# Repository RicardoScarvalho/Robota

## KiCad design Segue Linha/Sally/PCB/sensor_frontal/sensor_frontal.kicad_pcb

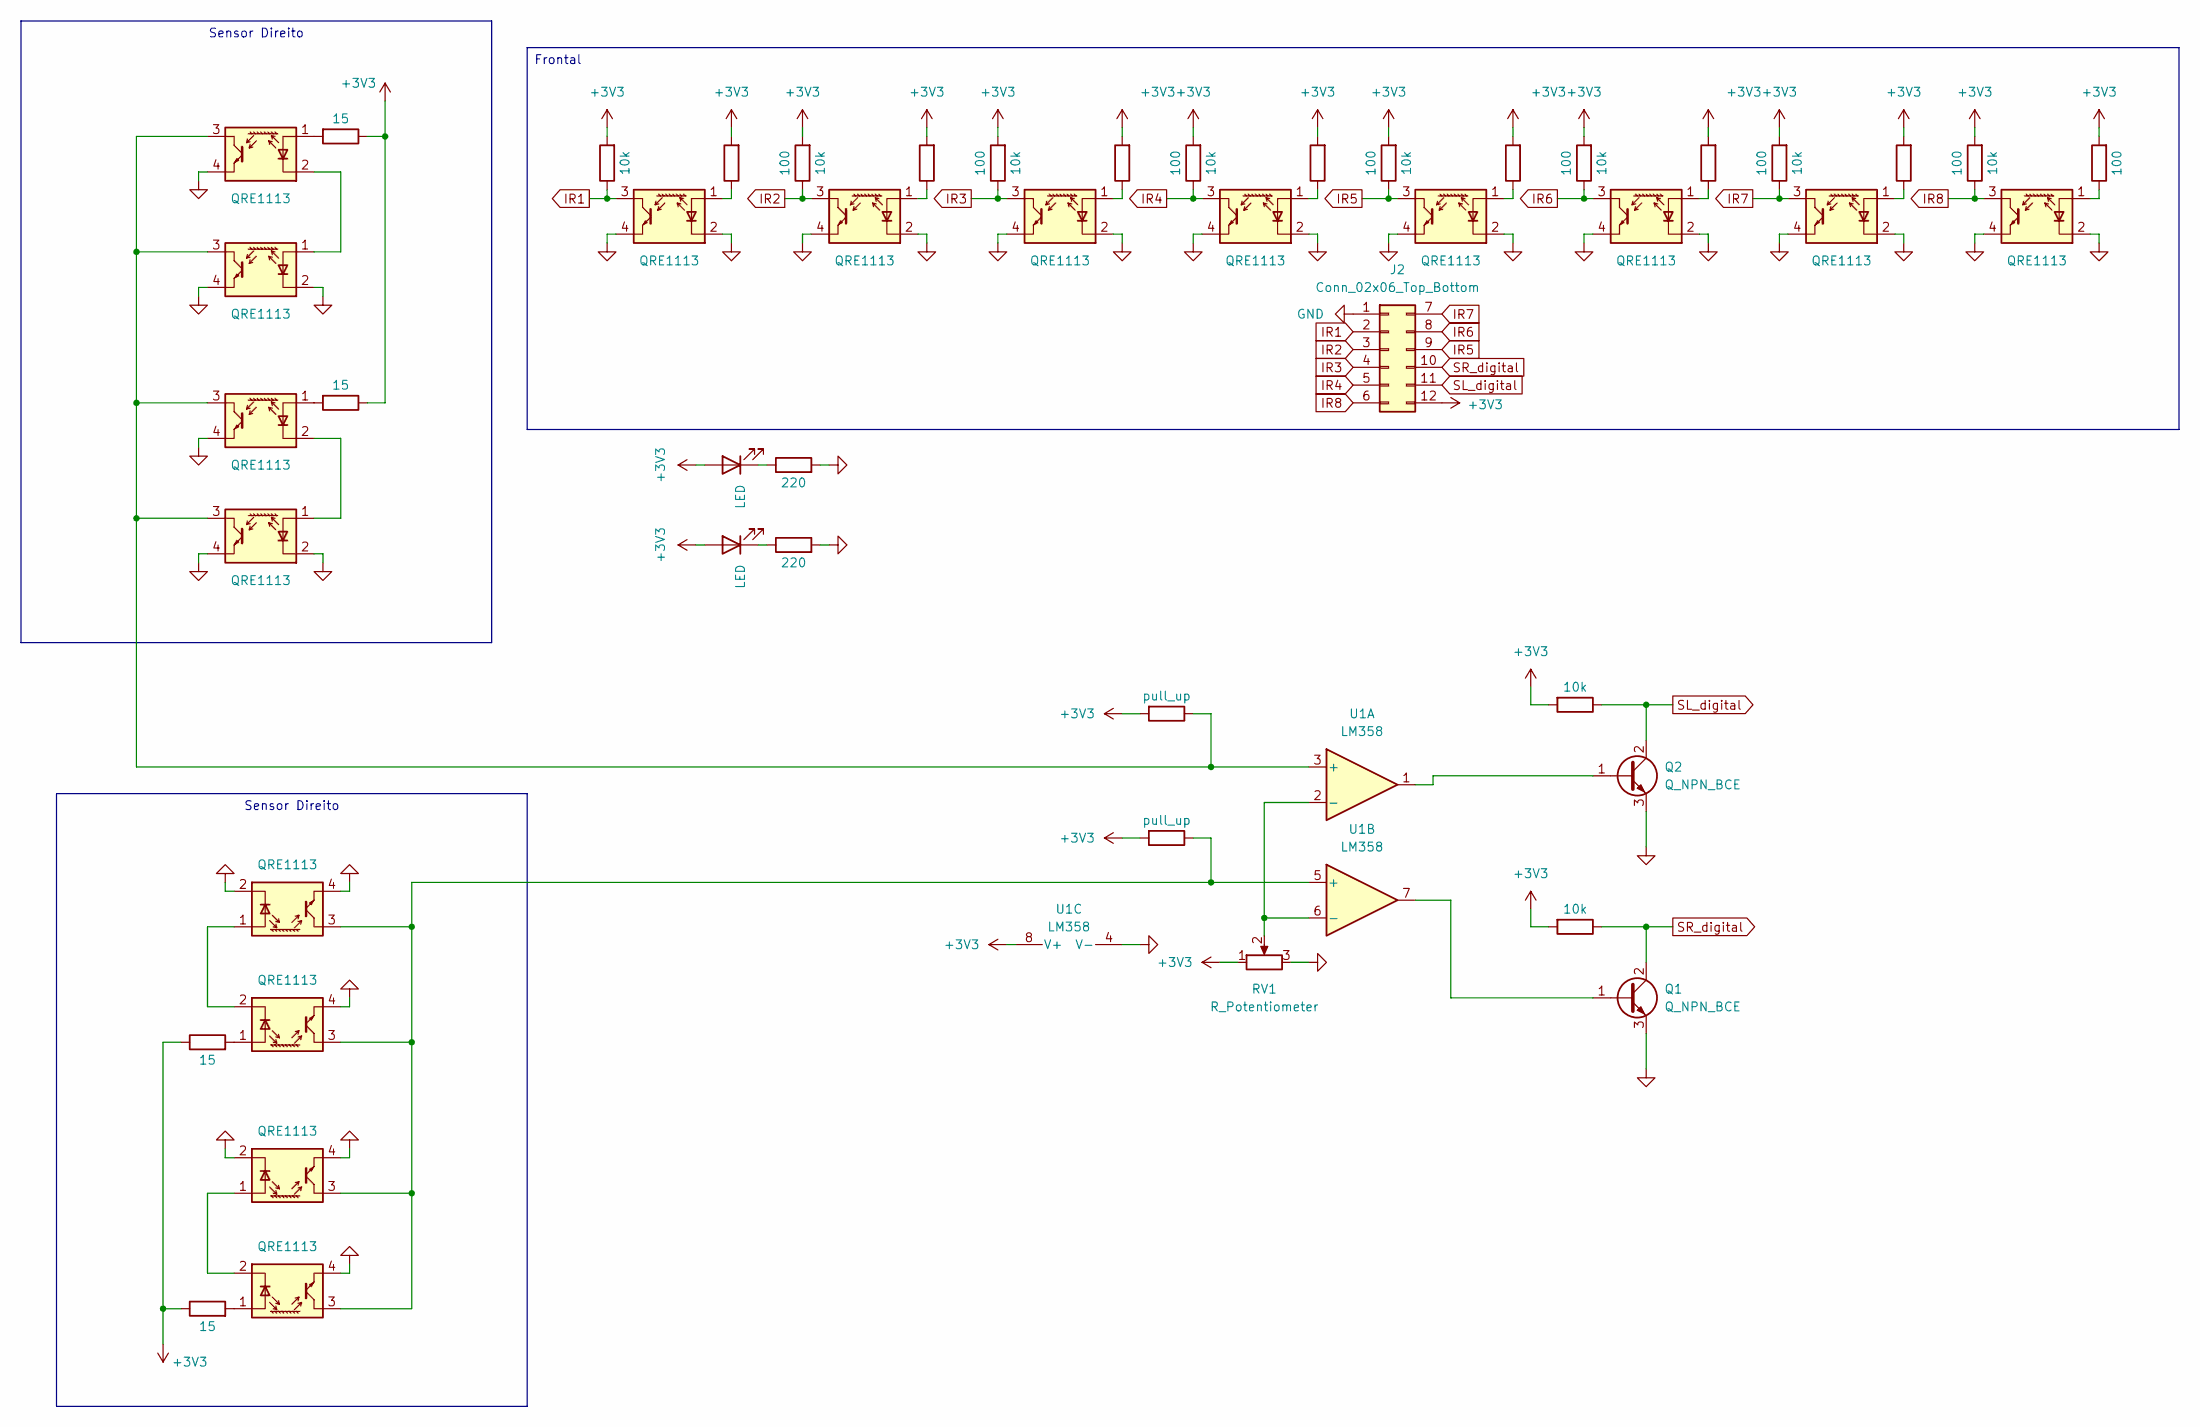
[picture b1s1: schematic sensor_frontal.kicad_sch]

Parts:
D4, D5: LED; LED_1206_3216Metric
J2: Conn_02x06_Top_Bottom; Hirose_FH12-12S-0.5SH_1x12-1MP_P0.50mm_Horizontal
Q1, Q2: Q_NPN_BCE; SOT-23
R11, R12, R29, R31, R32, R33, R34, R35, R44, R47: 10k; R_1206_3216Metric
R16, R18, R20, R21: 15; R_1206_3216Metric
R25, R26: 220; R_1206_3216Metric
R36, R37, R38, R39, R40, R41, R42, R43: 100; R_1206_3216Metric
R45, R46: pull_up; R_1206_3216Metric
RV1: R_Potentiometer; Potentiometer_Bourns_3314G_Vertical
U1: LM358; SOIC-8_3.9x4.9mm_P1.27mm
U5, U6, U7, U8, U11, U12, U13, U14, U15, U16, U17, U18, U19, U20, U21, U22: QRE1113; OnSemi_CASE100CY

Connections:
+3V3: D4.2 (A), D5.2 (A), J2.12, R11.2, R12.2, R16.1, R18.1, R20.1, R21.1, R29.2, R31.2, R32.2, R33.2, R34.2, R35.2, R36.2, R37.2, R38.2, R39.2, R40.2, R41.2, R42.2, R43.2, R44.2, R45.2, R46.2, R47.2, RV1.1, U1.8 (V+)
GND: J2.1, Q1.3 (E), Q2.3 (E), R25.2, R26.2, RV1.3, U1.4 (V-), U5.4, U6.2 (K), U6.4, U7.4, U8.2 (K), U8.4, U11.2 (K), U11.4, U12.4, U13.2 (K), U13.4, U14.4, U15.2 (K), U15.4, U16.2 (K), U16.4, U17.2 (K), U17.4, U18.2 (K), U18.4, U19.2 (K), U19.4, U20.2 (K), U20.4, U21.2 (K), U21.4, U22.2 (K), U22.4
IR1: J2.2, R11.1, U11.3
IR2: J2.3, R12.1, U16.3
IR3: J2.4, R29.1, U17.3
IR4: J2.5, R31.1, U18.3
IR5: J2.9, R32.1, U19.3
IR6: J2.8, R33.1, U20.3
IR7: J2.7, R34.1, U21.3
IR8: J2.6, R35.1, U22.3
unnamed: D4.1 (K), R25.1
unnamed: D5.1 (K), R26.1
unnamed: Q1.1 (B), U1.7
unnamed: Q2.1 (B), U1.1
unnamed: R45.1, U1.3 (+), U5.3, U6.3, U7.3, U8.3
unnamed: RV1.2, U1.2 (-), U1.6 (-)
unnamed: R46.1, U1.5 (+), U12.3, U13.3, U14.3, U15.3
unnamed: R18.2, U5.1 (A)
unnamed: U5.2 (K), U6.1 (A)
unnamed: R16.2, U7.1 (A)
unnamed: U7.2 (K), U8.1 (A)
unnamed: R36.1, U11.1 (A)
unnamed: R21.2, U12.1 (A)
unnamed: U12.2 (K), U13.1 (A)
unnamed: R20.2, U14.1 (A)
unnamed: U14.2 (K), U15.1 (A)
unnamed: R37.1, U16.1 (A)
unnamed: R38.1, U17.1 (A)
unnamed: R39.1, U18.1 (A)
unnamed: R40.1, U19.1 (A)
unnamed: R41.1, U20.1 (A)
unnamed: R42.1, U21.1 (A)
unnamed: R43.1, U22.1 (A)
SL_digital: J2.11, Q2.2 (C), R47.1
SR_digital: J2.10, Q1.2 (C), R44.1

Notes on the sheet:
Sensor Direito
Frontal

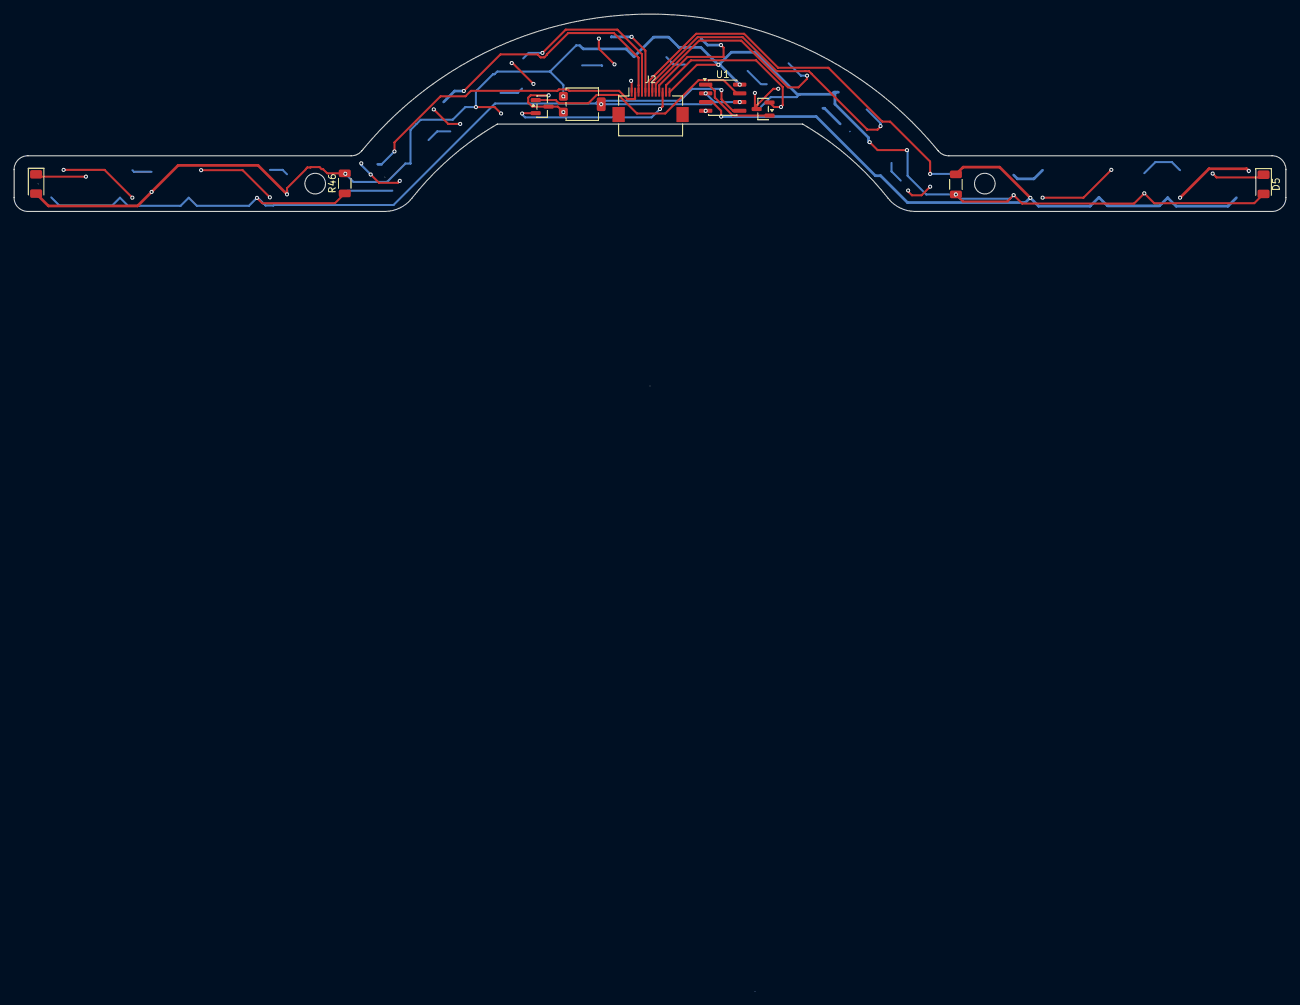
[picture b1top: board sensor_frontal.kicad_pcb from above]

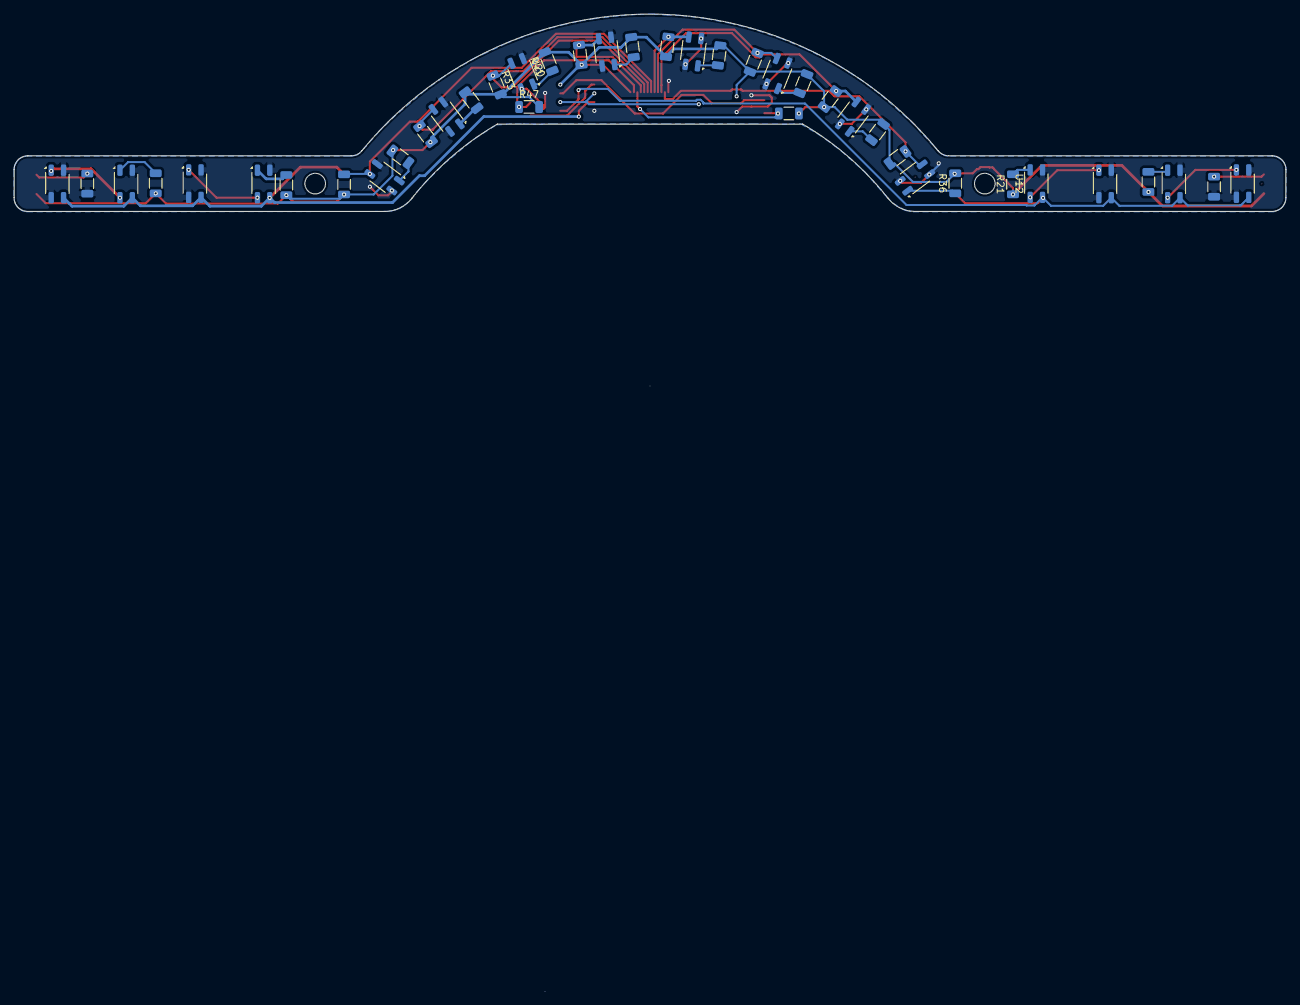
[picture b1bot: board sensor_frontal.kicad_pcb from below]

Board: 2 copper layers, 185.0 x 142.1 mm, 49 parts (40 on the bottom side), 35 nets.

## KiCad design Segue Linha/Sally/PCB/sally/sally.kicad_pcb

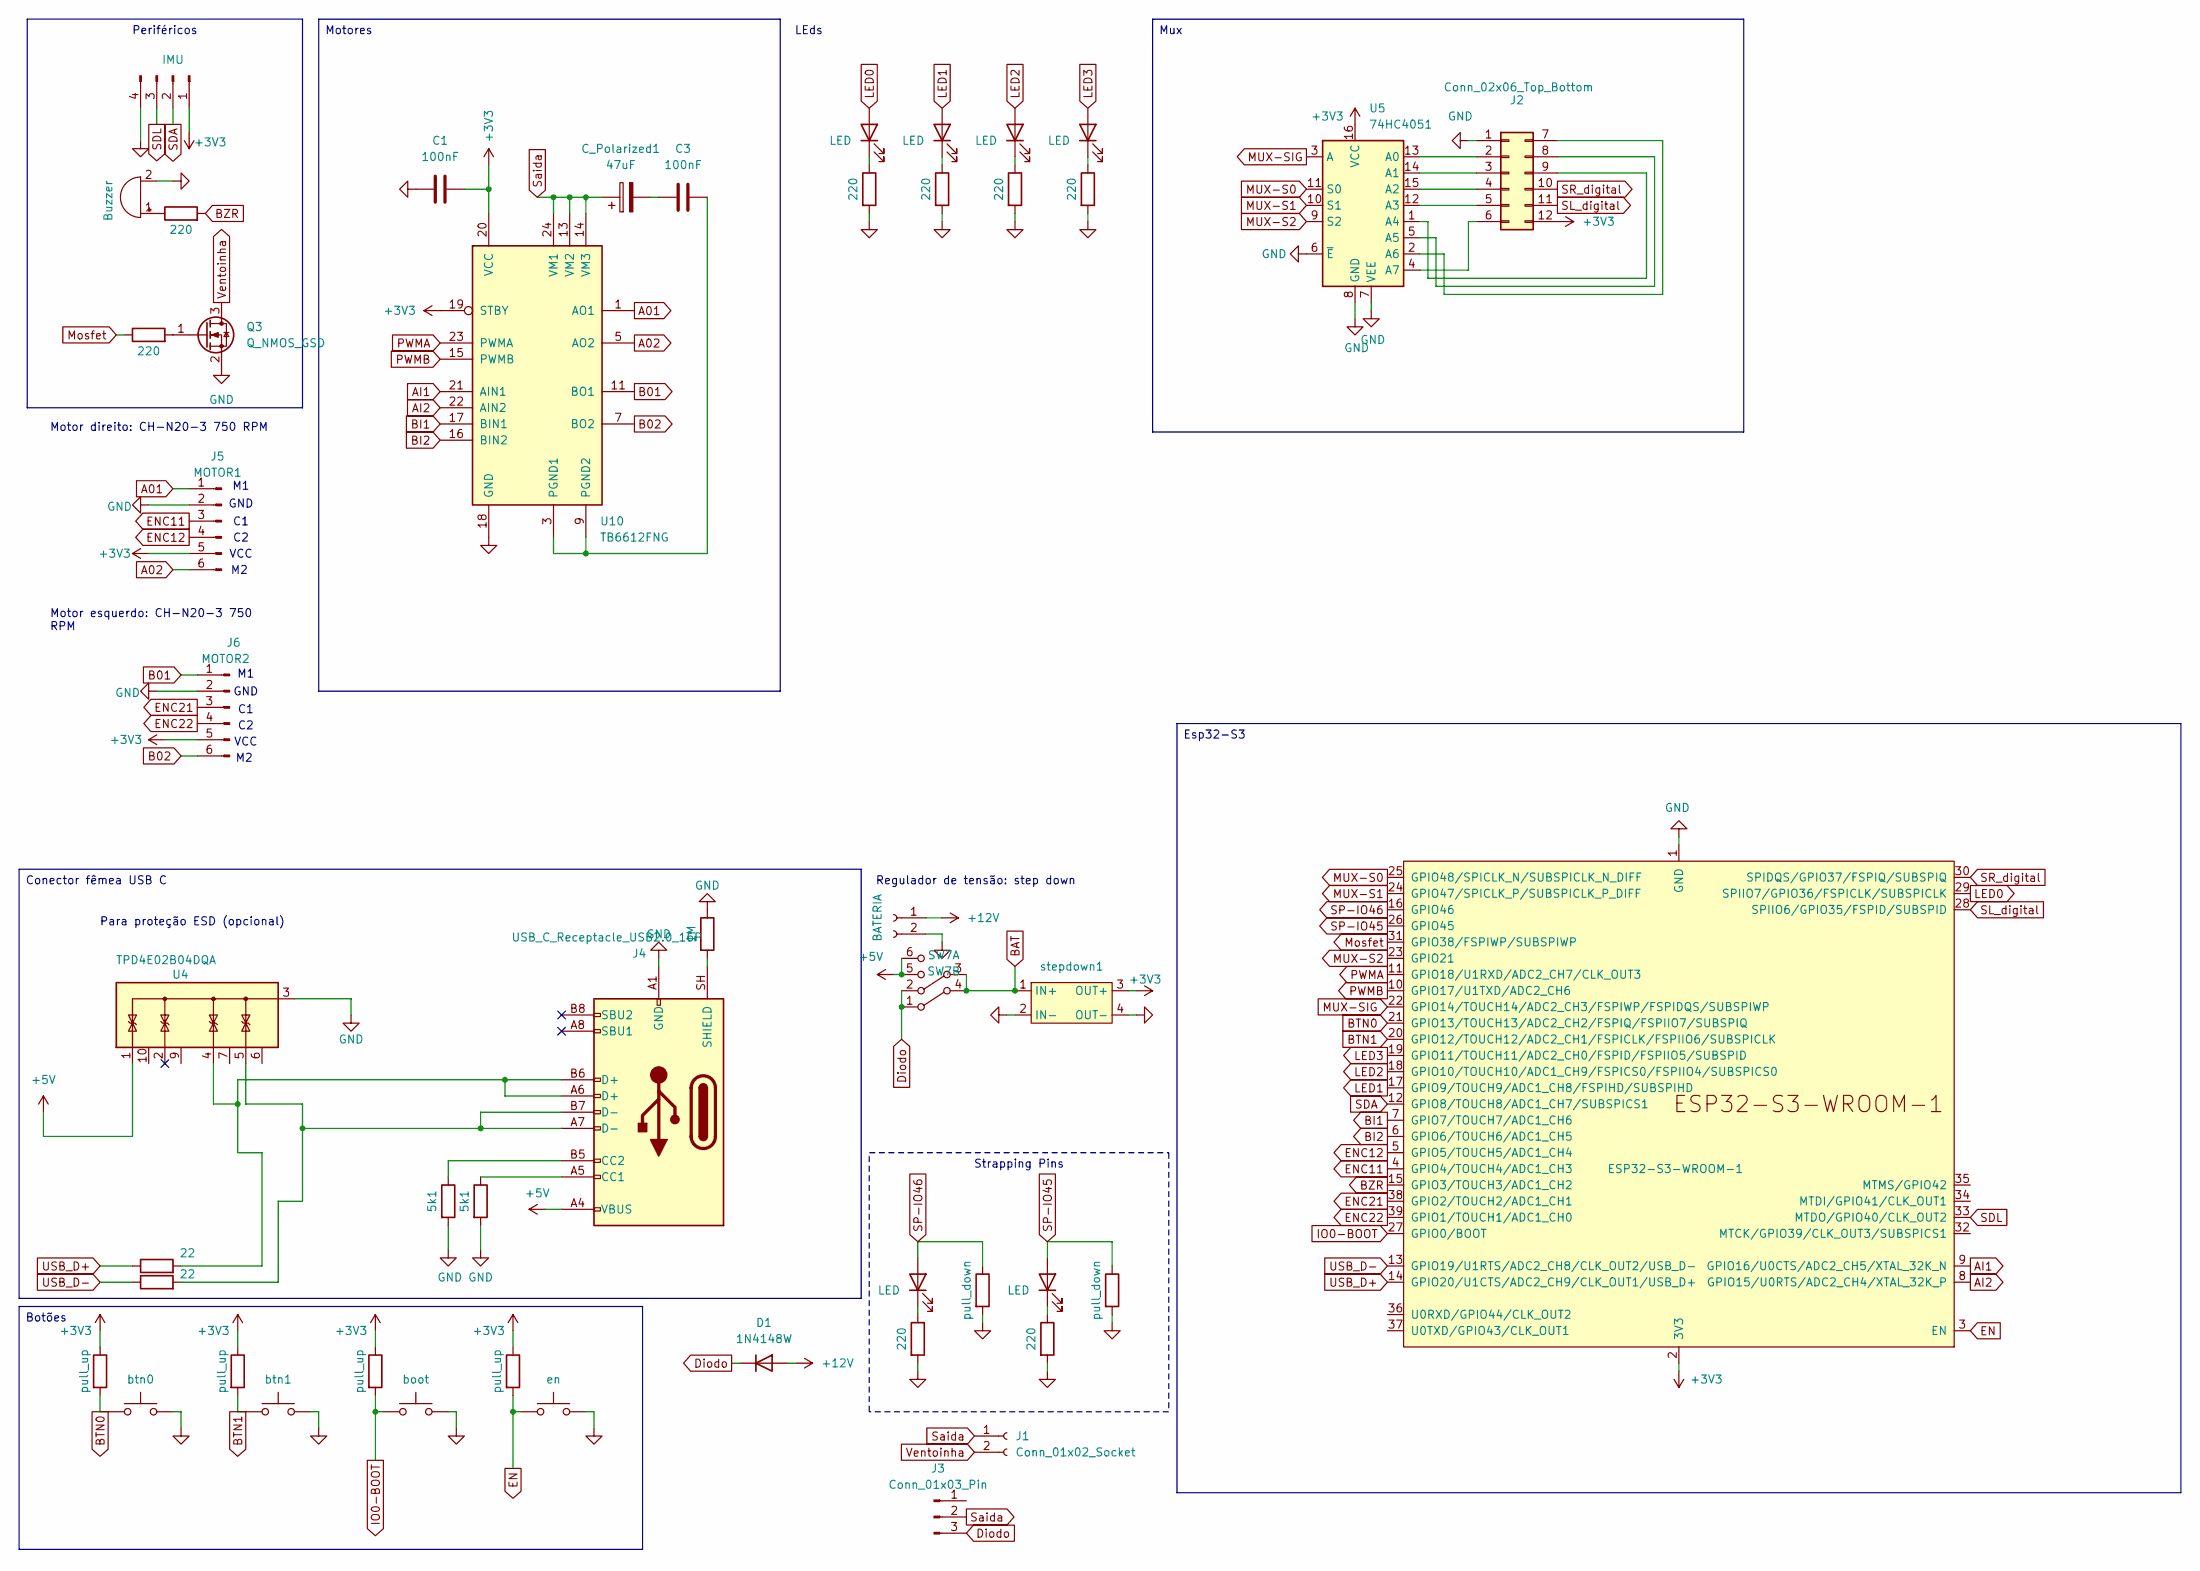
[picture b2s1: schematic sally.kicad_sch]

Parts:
BZ1: Buzzer; Buzzer_12x9.5RM7.6
C1, C3: 100nF; C_0805_2012Metric
C_Polarized1: 47uF; CP_Radial_D6.3mm_P2.50mm
D1: 1N4148W; D_SOD-123
D2, D3, D4, D5, D6, D7: LED; LED_1206_3216Metric
J1: Conn_01x02_Socket; PinHeader_1x02_P2.54mm_Vertical
J2: Conn_02x06_Top_Bottom; Hirose_FH12-12S-0.5SH_1x12-1MP_P0.50mm_Horizontal
J3: Conn_01x03_Pin; PinHeader_1x03_P2.54mm_Vertical
J4: USB_C_Receptacle_USB2.0_16P; USB_C_Receptacle_GCT_USB4085
J5: MOTOR1; PinHeader_1x06_P2.54mm_Vertical
J6: MOTOR2; PinHeader_1x06_P2.54mm_Vertical
Q3: Q_NMOS_GSD; SOT-23
R1, R3: 22; R_1206_3216Metric
R2, R24: 5k1; R_1206_3216Metric
R4, R6, R10, R25, R26, R27, R28, R30: 220; R_1206_3216Metric
R5, R7: pull_down; R_1206_3216Metric
R8, R9, R19, R22: pull_up; R_1206_3216Metric
R23: 1M; R_1206_3216Metric
SW1: btn0; SW_PUSH_6mm
SW2: btn1; SW_PUSH_6mm
SW3: boot; SW_PUSH_6mm
SW4: en; SW_PUSH_6mm
SW7: SW_DPDT_x2; PinHeader_2x03_P2.54mm_Vertical
U1: ESP32-S3-WROOM-1
U4: TPD4E02B04DQA; USON-10_2.5x1.0mm_P0.5mm
U5: 74HC4051; SOIC-16_3.9x9.9mm_P1.27mm
U10: TB6612FNG; SSOP-24_5.3x8.2mm_P0.65mm
con1: BATERIA; Molex_KK-254_AE-6410-02A_1x02_P2.54mm_Vertical
con6: IMU; PinHeader_1x04_P2.54mm_Vertical
stepdown1: stepdown

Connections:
+3V3: C1.2, J2.12, J5.5, J6.5, R8.1, R9.1, R19.1, R22.1, U1.2 (3V3), U5.16 (VCC), U10.19 (STBY), U10.20 (VCC), con6.1, stepdown1.3 (OUT+)
+5V: J4.A4 (VBUS), J4.A9 (VBUS), J4.B4 (VBUS), J4.B9 (VBUS), SW7.5 (C), SW7.6 (C), U4.1 (IO1)
+12V: D1.2 (A), con1.1
A01: J5.1, U10.1 (AO1), U10.2 (AO1)
A02: J5.6, U10.5 (AO2), U10.6 (AO2)
AI1: U1.9 (GPIO16/U0CTS/ADC2_CH5/XTAL_32K_N), U10.21 (AIN1)
AI2: U1.8 (GPIO15/U0RTS/ADC2_CH4/XTAL_32K_P), U10.22 (AIN2)
B01: J6.1, U10.11 (BO1), U10.12 (BO1)
B02: J6.6, U10.7 (BO2), U10.8 (BO2)
BAT: SW7.3 (B), SW7.4 (B), stepdown1.1 (IN+)
BI1: U1.7 (GPIO7/TOUCH7/ADC1_CH6), U10.17 (BIN1)
BI2: U1.6 (GPIO6/TOUCH6/ADC1_CH5), U10.16 (BIN2)
BTN0: R8.2, SW1.1, U1.21 (GPIO13/TOUCH13/ADC2_CH2/FSPIQ/FSPIIO7/S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)
BTN1: R9.2, SW2.1, U1.20 (GPIO12/TOUCH12/ADC2_CH1/FSPICLK/FSPIIO6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)
BZR: R10.2, U1.15 (GPIO3/TOUCH3/ADC1_CH2)
Diodo: D1.1 (K), J3.3, SW7.1 (A), SW7.2 (A)
EN: R22.2, SW4.1, U1.3 (EN)
ENC11: J5.3, U1.4 (GPIO4/TOUCH4/ADC1_CH3)
ENC12: J5.4, U1.5 (GPIO5/TOUCH5/ADC1_CH4)
ENC21: J6.3, U1.38 (GPIO2/TOUCH2/ADC1_CH1)
ENC22: J6.4, U1.39 (GPIO1/TOUCH1/ADC1_CH0)
GND: BZ1.2 (+), C1.1, J2.1, J4.A1 (GND), J4.A12 (GND), J4.B1 (GND), J4.B12 (GND), J5.2, J6.2, Q3.2 (S), R2.2, R4.2, R5.2, R6.2, R7.2, R23.1, R24.2, R25.2, R26.2, R27.2, R28.2, SW1.2, SW2.2, SW3.2, SW4.2, U1.1 (GND), U1.40 (GND), U1.41 (GND), U4.3 (G), U4.8 (G), U5.6 (~E), U5.7 (VEE), U5.8 (GND), U10.18 (GND), con1.2, con6.4, stepdown1.2 (IN-), stepdown1.4 (OUT-)
IO0-BOOT: R19.2, SW3.1, U1.27 (GPIO0/BOOT)
LED0: D4.2 (A), U1.29 (SPIIO7/GPIO36/FSPICLK/SUBSPICLK)
LED1: D5.2 (A), U1.17 (GPIO9/TOUCH9/ADC1_CH8/FSPIHD/SUBSPIHD)
LED2: D6.2 (A), U1.18 (GPIO10/TOUCH10/ADC1_CH9/FSPICS0/FSPIIO4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)
LED3: D7.2 (A), U1.19 (GPIO11/TOUCH11/ADC2_CH0/FSPID/FSPIIO5/S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)
MUX-S0: U1.25 (GPIO48/SPICLK_N/SUBSPICLK_N_DIFF), U5.11 (S0)
MUX-S1: U1.24 (GPIO47/SPICLK_P/SUBSPICLK_P_DIFF), U5.10 (S1)
MUX-S2: U1.23 (GPIO21), U5.9 (S2)
MUX-SIG: U1.22 (GPIO14/TOUCH14/ADC2_CH3/FSPIWP/FSPIDQS/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), U5.3 (A)
Mosfet: R30.1, U1.31 (GPIO38/FSPIWP/SUBSPIWP)
unnamed: BZ1.1 (-), R10.1
unnamed: C3.1, C_Polarized1.2
unnamed: C3.2, U10.3 (PGND1), U10.4 (PGND1), U10.9 (PGND2), U10.10 (PGND2)
unnamed: D2.1 (K), R4.1
unnamed: D3.1 (K), R6.1
unnamed: D4.1 (K), R25.1
unnamed: D5.1 (K), R26.1
unnamed: D6.1 (K), R27.1
unnamed: D7.1 (K), R28.1
unnamed: J2.2, U5.13 (A0)
unnamed: J2.3, U5.14 (A1)
unnamed: J2.4, U5.15 (A2)
unnamed: J2.5, U5.12 (A3)
unnamed: J2.6, U5.4 (A7)
unnamed: J2.7, U5.2 (A6)
unnamed: J2.8, U5.5 (A5)
unnamed: J2.9, U5.1 (A4)
unnamed: J4.A5 (CC1), R2.1
unnamed: J4.B5 (CC2), R24.1
unnamed: J4.SH (SHIELD), R23.2
unnamed: Q3.1 (G), R30.2
unnamed: J4.A6 (D+), J4.B6 (D+), R3.2, U4.4 (IO3)
unnamed: J4.A7 (D-), J4.B7 (D-), R1.2, U4.5 (IO4)
PWMA: U1.11 (GPIO18/U1RXD/ADC2_CH7/CLK_OUT3), U10.23 (PWMA)
PWMB: U1.10 (GPIO17/U1TXD/ADC2_CH6), U10.15 (PWMB)
SDA: U1.12 (GPIO8/TOUCH8/ADC1_CH7/SUBSPICS1), con6.2
SDL: U1.33 (MTDO/GPIO40/CLK_OUT2), con6.3
SL_digital: J2.11, U1.28 (SPIIO6/GPIO35/FSPID/SUBSPID)
SP-IO45: D3.2 (A), R7.1, U1.26 (GPIO45)
SP-IO46: D2.2 (A), R5.1, U1.16 (GPIO46)
SR_digital: J2.10, U1.30 (SPIDQS/GPIO37/FSPIQ/SUBSPIQ)
Saida: C_Polarized1.1, J1.1, J3.2, U10.13 (VM2), U10.14 (VM3), U10.24 (VM1)
USB_D+: R3.1, U1.14 (GPIO20/U1CTS/ADC2_CH9/CLK_OUT1/USB_D+)
USB_D-: R1.1, U1.13 (GPIO19/U1RTS/ADC2_CH8/CLK_OUT2/USB_D-)
Ventoinha: J1.2, Q3.3 (D)

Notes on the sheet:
VCC
GND
Para proteção ESD (opcional)
Esp32-S3
Periféricos
Motores
LEds
Regulador de tensão: step down
Conector fêmea USB C
Botões
Strapping Pins
Mux
Motor esquerdo: CH-N20-3 750 RPM
Motor direito: CH-N20-3 750 RPM

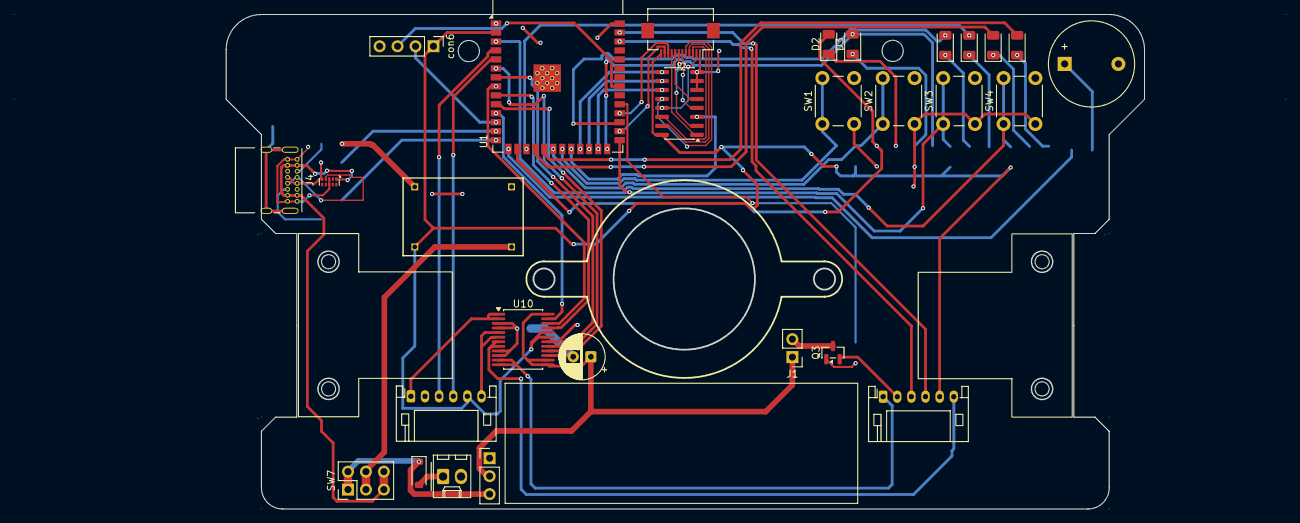
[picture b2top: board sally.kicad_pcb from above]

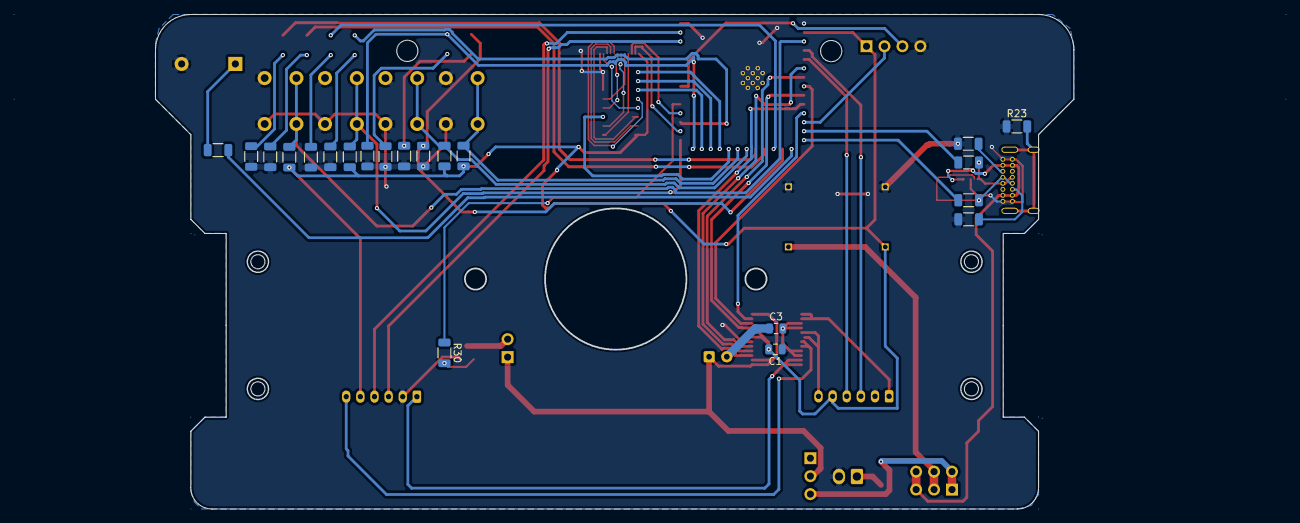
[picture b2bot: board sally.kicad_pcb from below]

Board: 2 copper layers, 179.8 x 69.8 mm, 51 parts (21 on the bottom side), 67 nets.

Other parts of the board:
Suporte_dos_motores_1, Suporte_dos_motores_2: suporte
